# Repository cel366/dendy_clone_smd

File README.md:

# Деndи
Конструкция 8-ми битной приставки ,клона famicom. Максимально элементы применены для поверхностного монтажа . Печатная плата разработана для изготовления в домашних условиях ,поэтому для соединения дорожек на разных слоях использованы переходные отверстия ,для соединениями перемычками .  в папке FAB/lut два файла svg  с слоями верхним(уже от зеркаленным) и нижним  

Плата размером 90х90 ,чтобы можно было потом распечатать на принтере EasyThreeD K9 , у которого печатающая поверхность  100х100,корпус.

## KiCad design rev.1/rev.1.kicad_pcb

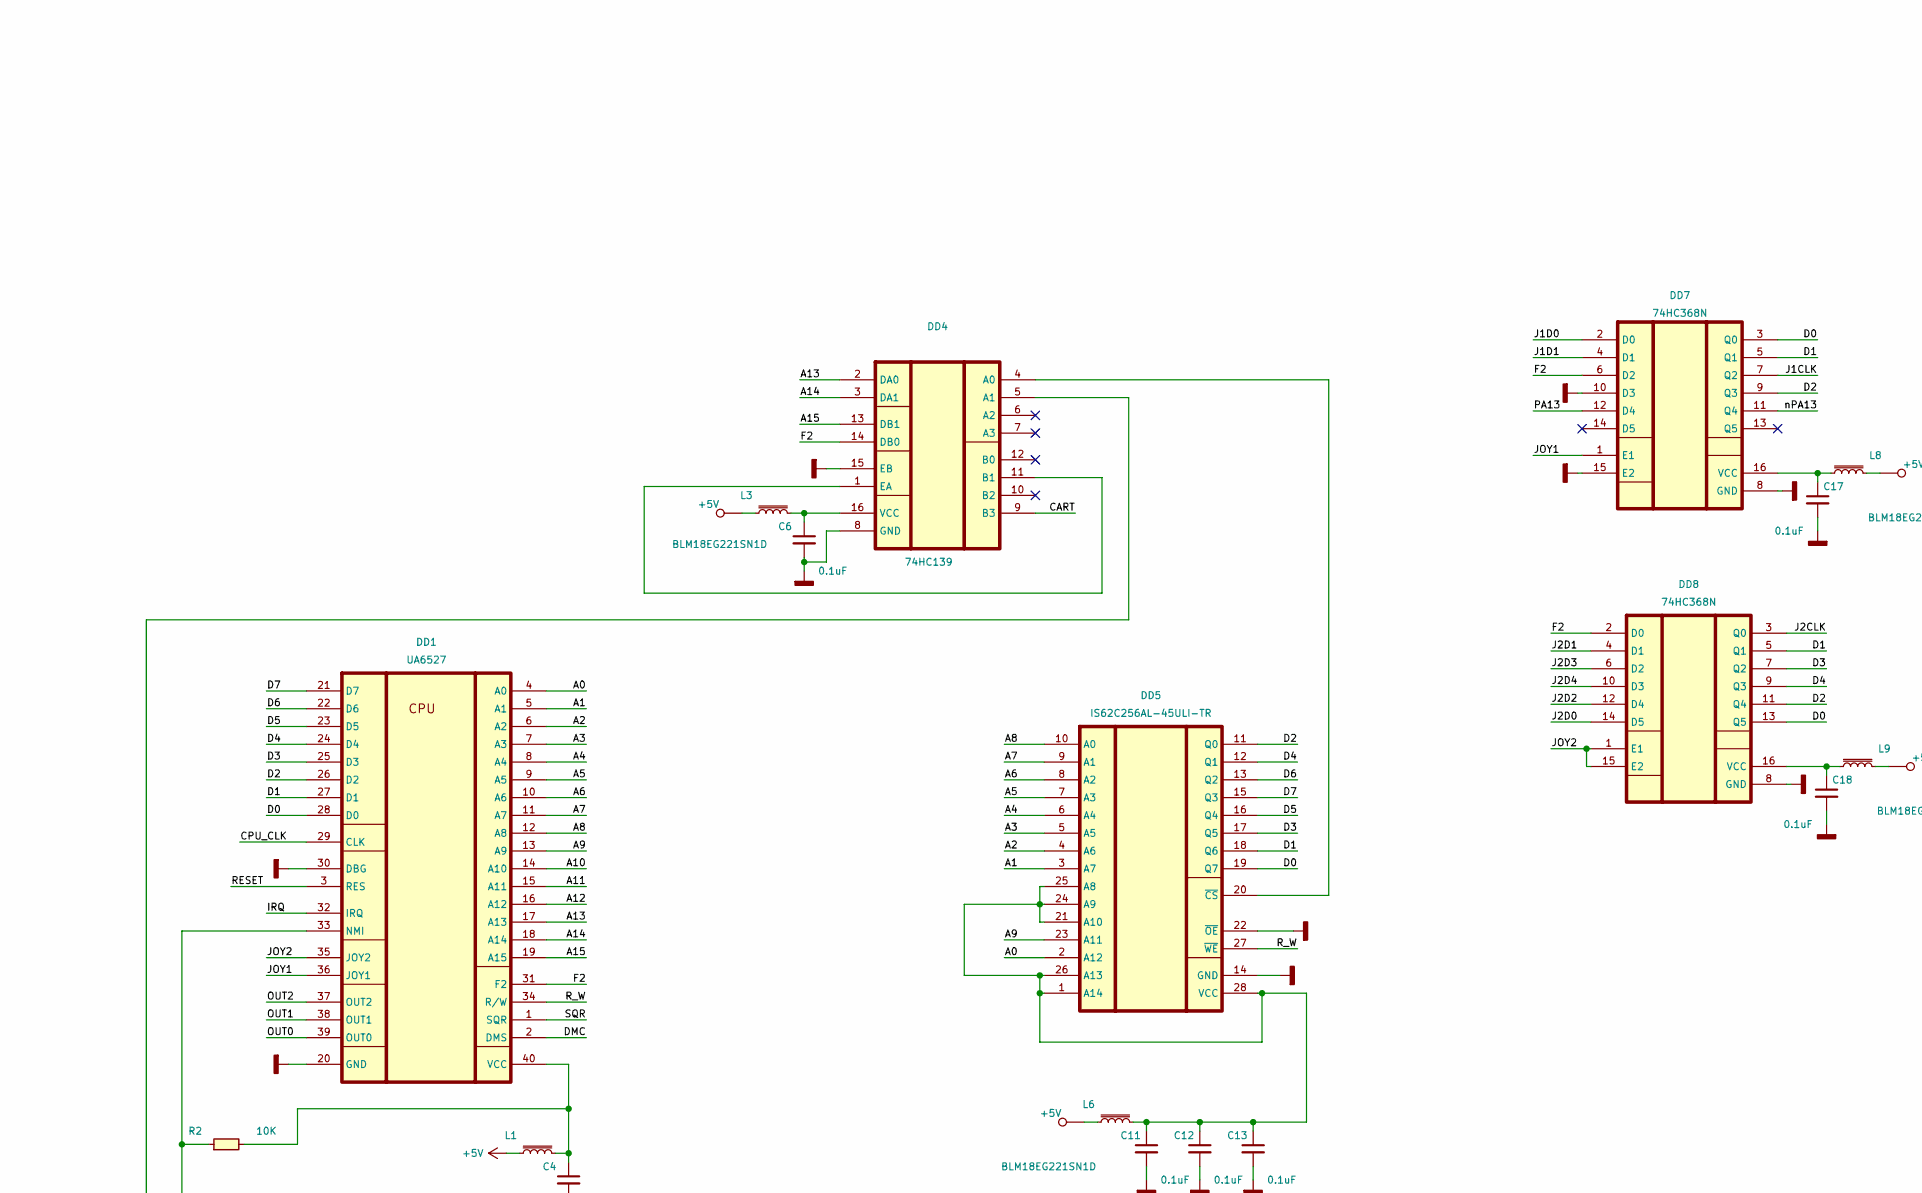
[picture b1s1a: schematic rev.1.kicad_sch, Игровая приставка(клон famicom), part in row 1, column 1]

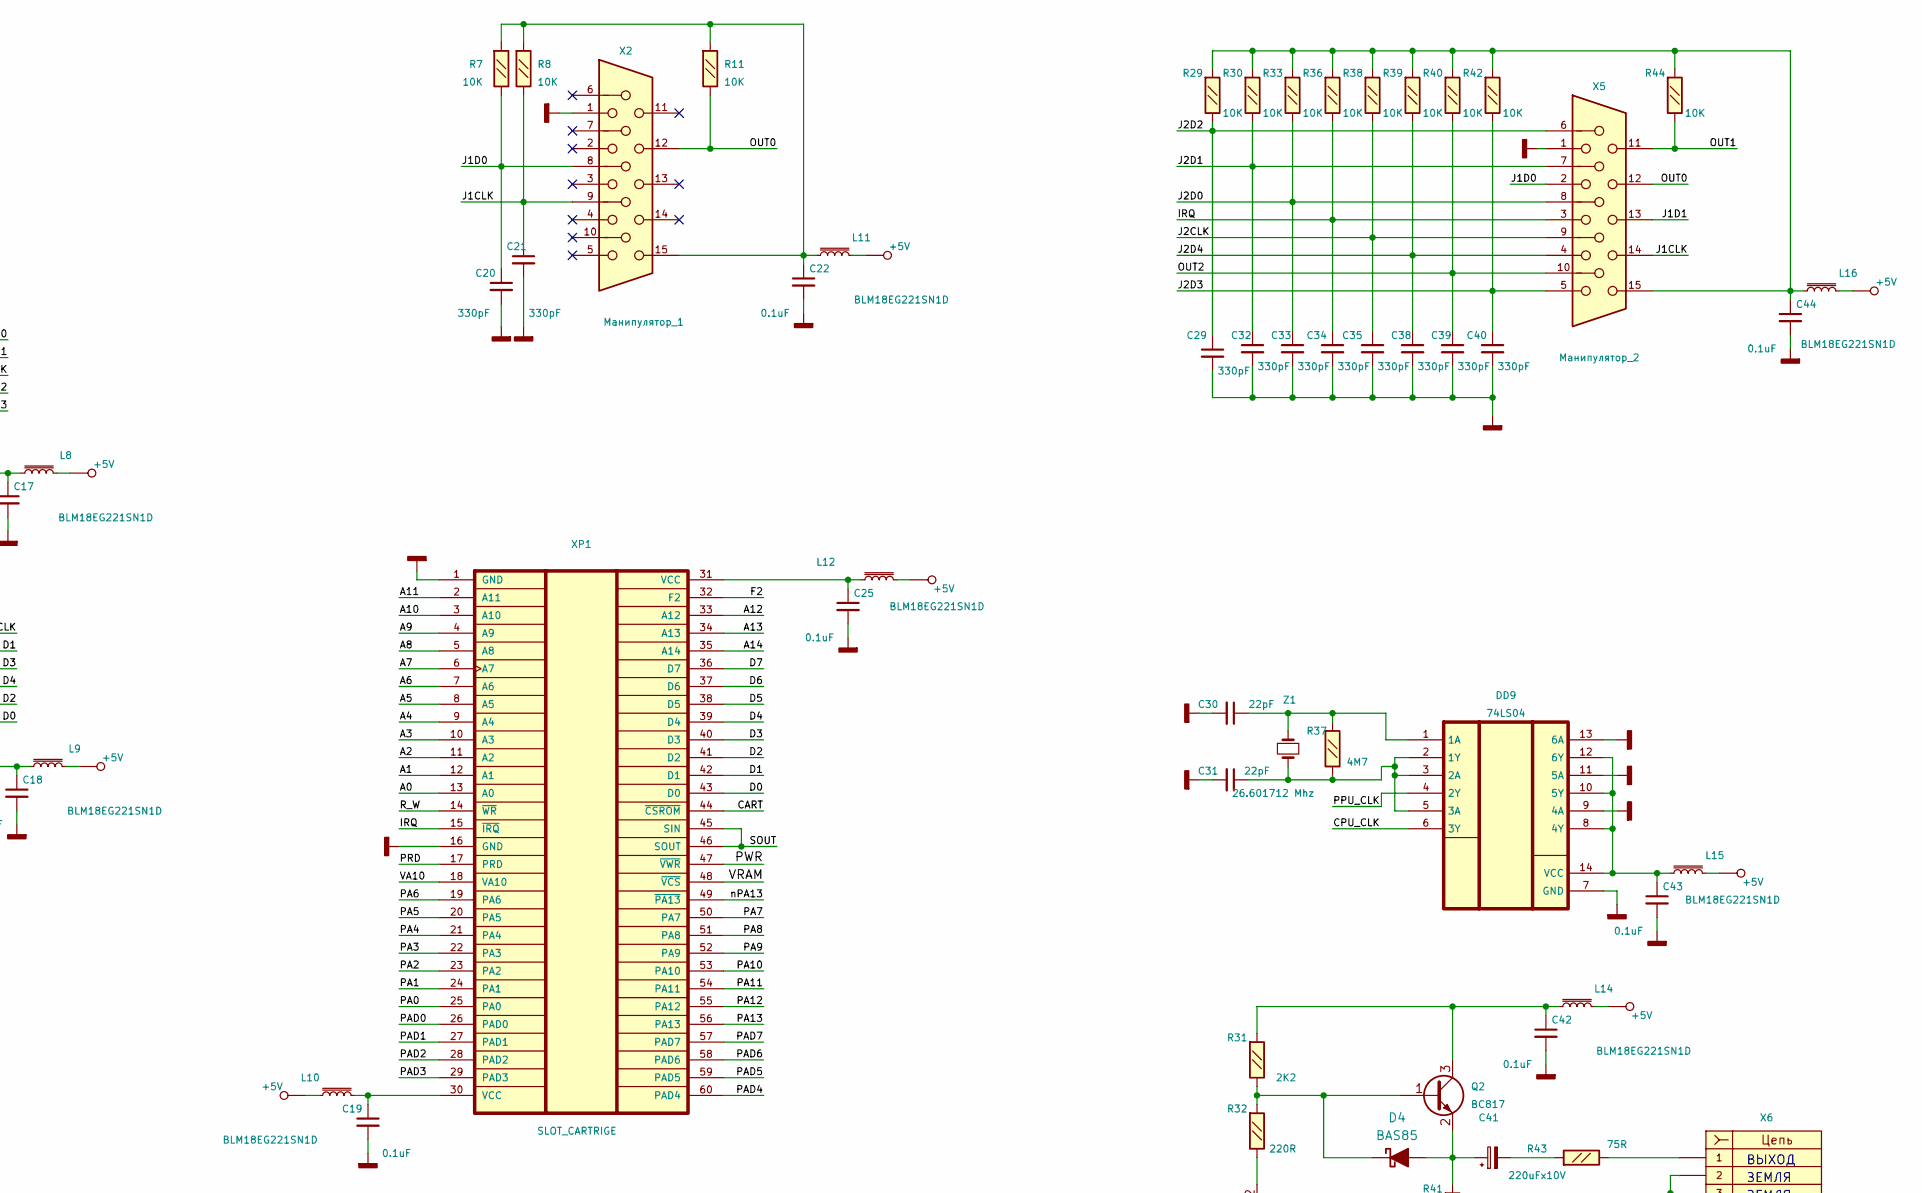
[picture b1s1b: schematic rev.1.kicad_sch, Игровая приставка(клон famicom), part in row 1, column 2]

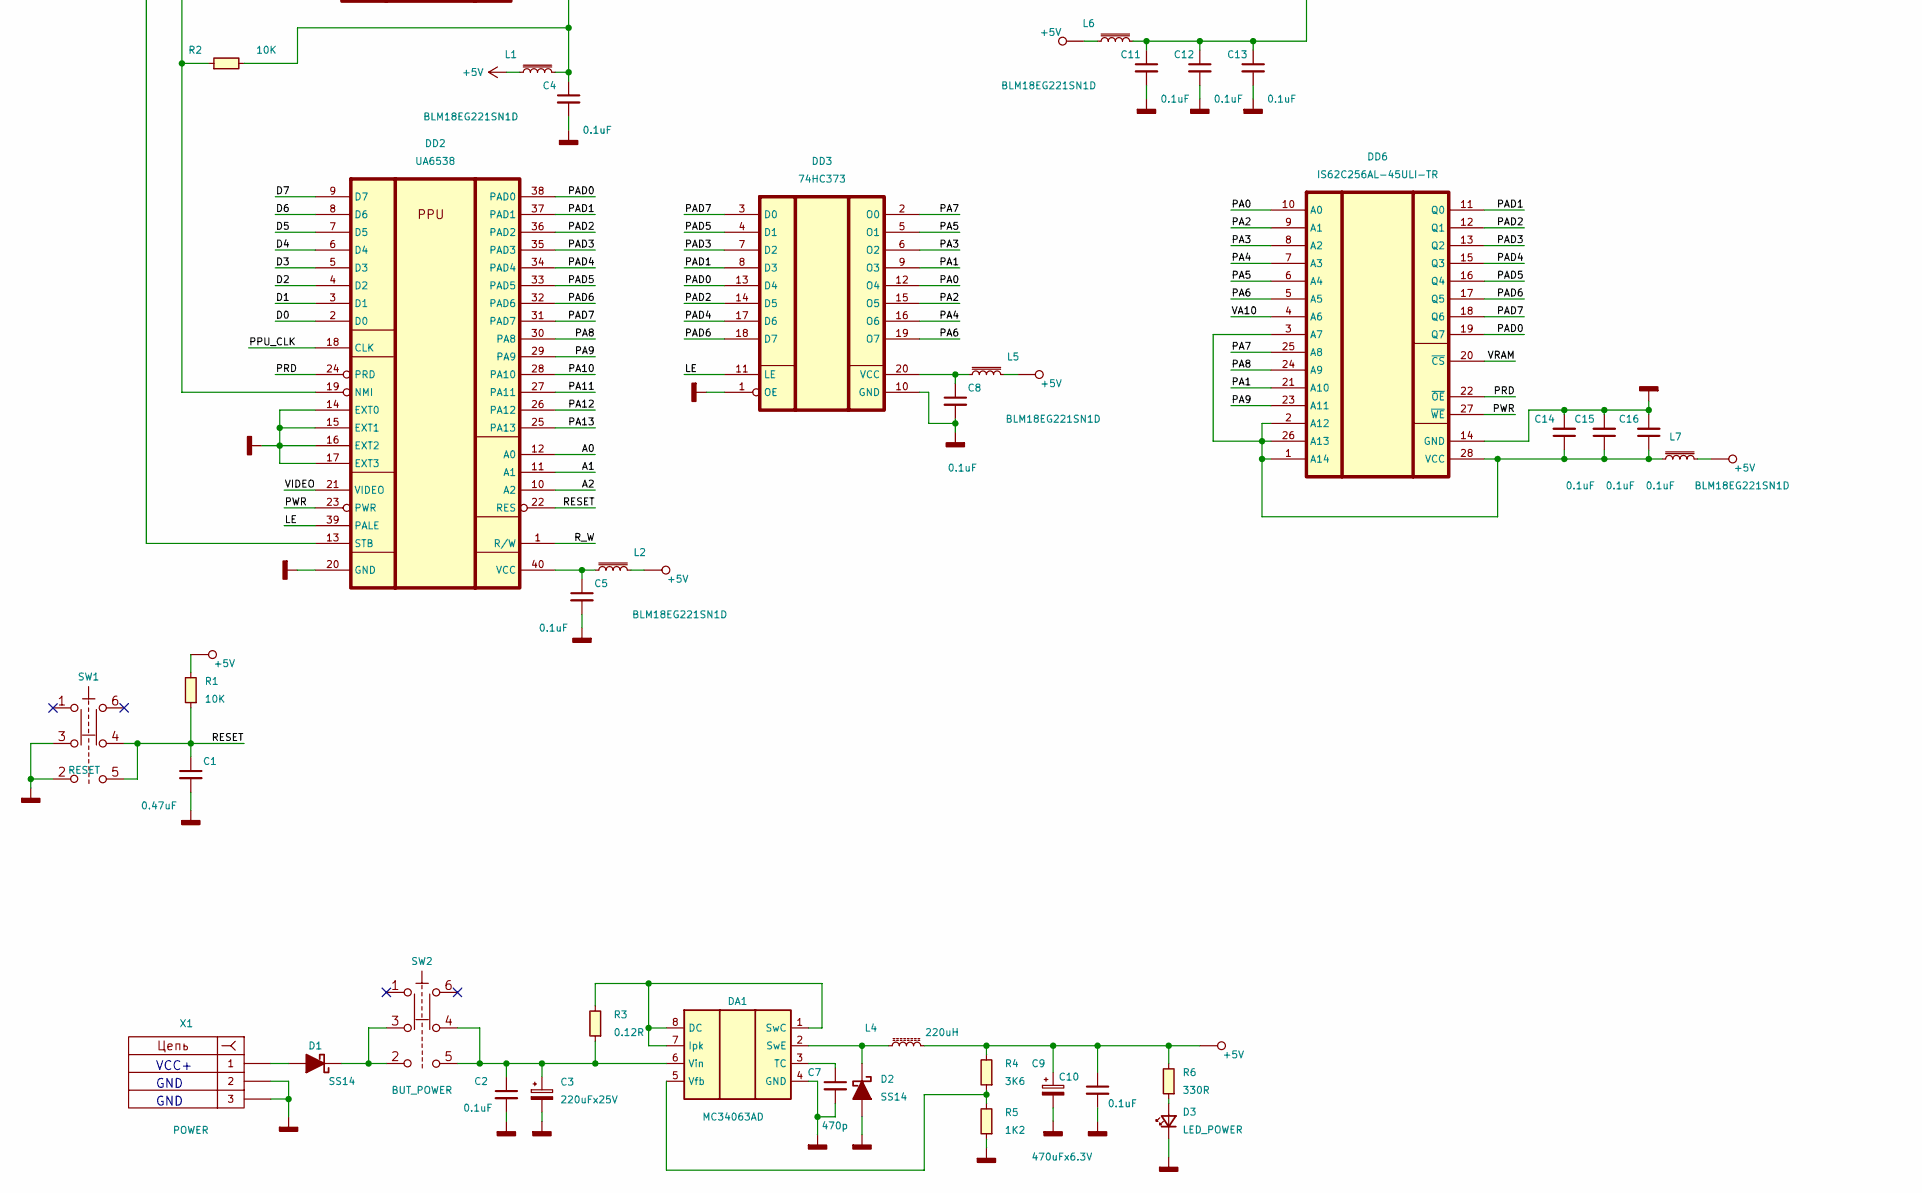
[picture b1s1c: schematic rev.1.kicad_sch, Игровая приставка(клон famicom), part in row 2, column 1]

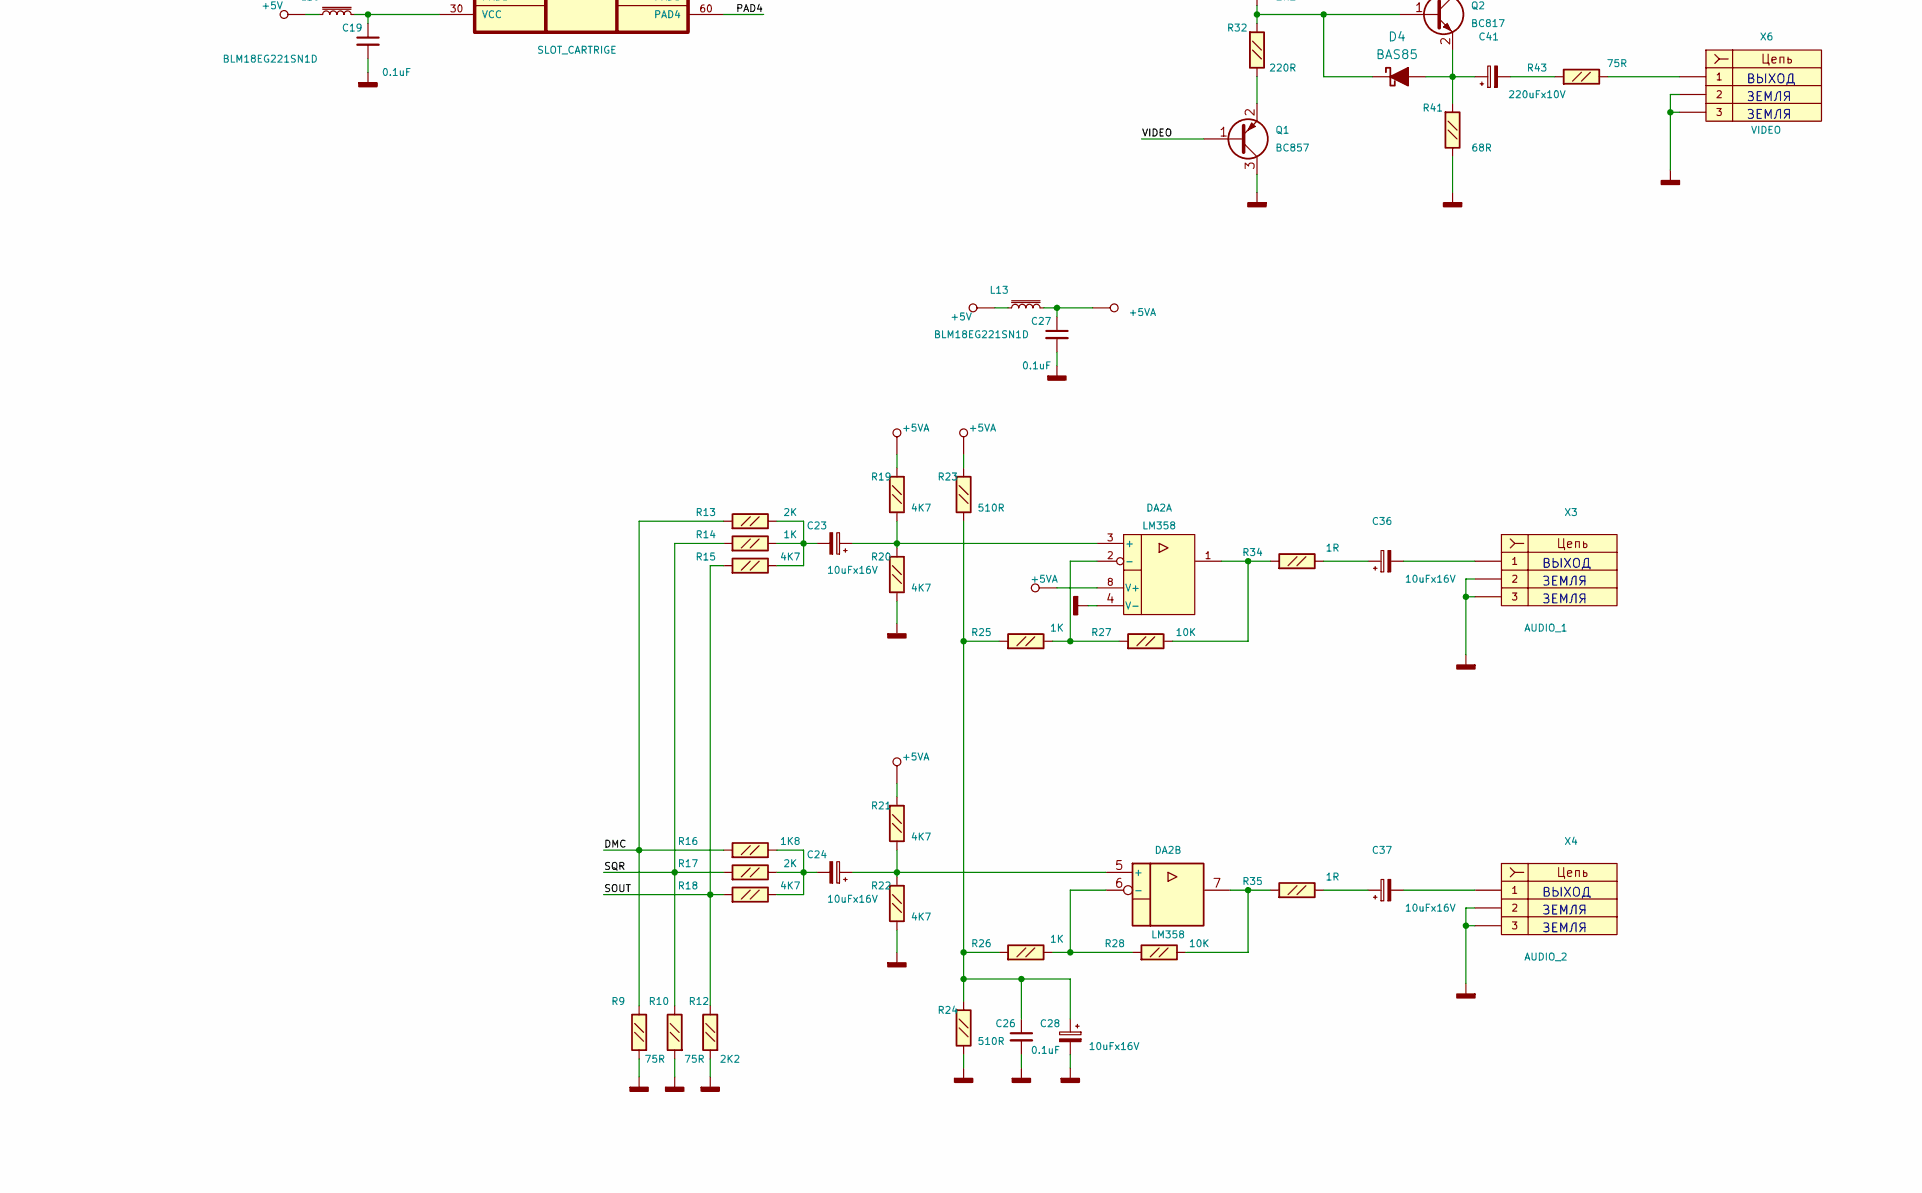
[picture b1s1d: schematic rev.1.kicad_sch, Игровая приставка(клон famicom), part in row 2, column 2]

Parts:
C1: 0.47uF; C_0603_1608Metric
C2, C4, C5, C6, C8, C10, C11, C12, C13, C14, C15, C16, C17, C18, C19, C22, C25, C26, C27, C42, C43, C44: 0.1uF; C_0603_1608Metric
C3: 220uFx25V; CP_Elec_8x10.5
C7: 470p; C_0603_1608Metric
C9: 470uFx6.3V; CP_Elec_8x10.5
C20, C21, C29, C32, C33, C34, C35, C38, C39, C40: 330pF; C_0603_1608Metric
C23, C24, C28, C36, C37: 10uFx16V; CP_Elec_4x5.4
C30, C31: 22pF; C_0603_1608Metric
C41: 220uFx10V; CP_Elec_8x6.5
D1, D2: SS14; D_SMA
D3: LED_POWER; LED_D3.0mm
D4: BAS85; D_MiniMELF
DA1: MC34063AD; SOIC-8_3.9x4.9mm_P1.27mm
DA2: LM358; SOIC-8_3.9x4.9mm_P1.27mm
DD1: UA6527; DIP-40_W15.24mm_Socket
DD2: UA6538; DIP-40_W15.24mm_Socket
DD3: 74HC373; SO-20_12.8x7.5mm_P1.27mm
DD4: 74HC139; SO-16_3.9x9.9mm_P1.27mm
DD5, DD6: IS62C256AL-45ULI-TR; SOIC-28W_7.5x17.9mm_P1.27mm
DD7, DD8: 74HC368N; SO-16_3.9x9.9mm_P1.27mm
DD9: 74LS04; SO-14_3.9x8.65mm_P1.27mm
L1, L2, L3, L5, L6, L7, L8, L9, L10, L11, L12, L13, L14, L15, L16: BLM18EG221SN1D; L_0603_1608Metric
L4: 220uH; L_Radial_D7.0mm_P3.00mm
Q1: BC857; SOT-23
Q2: BC817; SOT-23
R1, R2, R7, R8, R11, R27, R28, R29, R30, R33, R36, R38, R39, R40, R42, R44: 10K; R_0603_1608Metric
R3: 0.12R; R_0603_1608Metric
R4: 3K6; R_0603_1608Metric
R5: 1K2; R_0603_1608Metric
R6: 330R; R_0603_1608Metric
R9, R10, R43: 75R; R_0603_1608Metric
R12, R31: 2K2; R_0603_1608Metric
R13, R17: 2K; R_0603_1608Metric
R14, R25, R26: 1K; R_0603_1608Metric
R15, R18, R19, R20, R21, R22: 4K7; R_0603_1608Metric
R16: 1K8; R_0603_1608Metric
R23, R24: 510R; R_0603_1608Metric
R32: 220R; R_0603_1608Metric
R34, R35: 1R; R_0603_1608Metric
R37: 4M7; R_0603_1608Metric
R41: 68R; R_0603_1608Metric
SW1: RESET; KLS7_P8X8
SW2: BUT_POWER; KLS7_P8X8
X1: POWER; BarrelJack_Wuerth_6941xx301002
X2: Манипулятор_1; DSUB-15_Male_Horizontal_P2.77x2.84mm_EdgePinOffset4.94mm_Ho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
X3: AUDIO_1; RCA-105
X4: AUDIO_2; RCA-105
X5: Манипулятор_2; DSUB-15_Male_Horizontal_P2.77x2.84mm_EdgePinOffset4.94mm_Ho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
X6: VIDEO; RCA-105
XP1: SLOT_CARTRIGE; 60 PIN FAMICOM CARTRIDGE SLOT
Z1: 26.601712 Mhz; Crystal_SMD_HC49-SD

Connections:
+5V: C9.1, C10.1, L1.1, L2.1, L3.1, L4.2, L5.1, L6.1, L7.1, L8.1, L9.1, L10.1, L11.1, L12.1, L13.1, L14.1, L15.1, L16.1, R1.2, R4.2, R6.2
+5VA: C27.1, DA2.8 (V+), L13.2, R19.2, R21.2, R23.2
/A0: DD1.4 (A0), DD2.12 (A0), DD5.2 (A12), XP1.13 (A0)
/A1: DD1.5 (A1), DD2.11 (A1), DD5.3 (A7), XP1.12 (A1)
/A2: DD1.6 (A2), DD2.10 (A2), DD5.4 (A6), XP1.11 (A2)
/A3: DD1.7 (A3), DD5.5 (A5), XP1.10 (A3)
/A4: DD1.8 (A4), DD5.6 (A4), XP1.9 (A4)
/A5: DD1.9 (A5), DD5.7 (A3), XP1.8 (A5)
/A6: DD1.10 (A6), DD5.8 (A2), XP1.7 (A6)
/A7: DD1.11 (A7), DD5.9 (A1), XP1.6 (A7)
/A8: DD1.12 (A8), DD5.10 (A0), XP1.5 (A8)
/A9: DD1.13 (A9), DD5.23 (A11), XP1.4 (A9)
/A10: DD1.14 (A10), XP1.3 (A10)
/A11: DD1.15 (A11), XP1.2 (A11)
/A12: DD1.16 (A12), XP1.33 (A12)
/A13: DD1.17 (A13), DD4.2 (DA0), XP1.34 (A13)
/A14: DD1.18 (A14), DD4.3 (DA1), XP1.35 (A14)
/A15: DD1.19 (A15), DD4.13 (DB1)
/CART: DD4.9 (B3), XP1.44 (~CSROM)
/CPU_CLK: DD1.29 (CLK), DD9.6 (3Y)
/D0: DD1.28 (D0), DD2.2 (D0), DD5.19 (Q7), DD7.3 (Q0), DD8.13 (Q5), XP1.43 (D0)
/D1: DD1.27 (D1), DD2.3 (D1), DD5.18 (Q6), DD7.5 (Q1), DD8.5 (Q1), XP1.42 (D1)
/D2: DD1.26 (D2), DD2.4 (D2), DD5.11 (Q0), DD7.9 (Q3), DD8.11 (Q4), XP1.41 (D2)
/D3: DD1.25 (D3), DD2.5 (D3), DD5.17 (Q5), DD8.7 (Q2), XP1.40 (D3)
/D4: DD1.24 (D4), DD2.6 (D4), DD5.12 (Q1), DD8.9 (Q3), XP1.39 (D4)
/D5: DD1.23 (D5), DD2.7 (D5), DD5.16 (Q4), XP1.38 (D5)
/D6: DD1.22 (D6), DD2.8 (D6), DD5.13 (Q2), XP1.37 (D6)
/D7: DD1.21 (D7), DD2.9 (D7), DD5.15 (Q3), XP1.36 (D7)
/DMC: DD1.2 (DMS), R9.1, R13.2, R16.2
/F2: DD1.31 (F2), DD4.14 (DB0), DD7.6 (D2), DD8.2 (D0), XP1.32 (F2)
/IRQ: C34.1, DD1.32 (IRQ), R36.1, X5.3, XP1.15 (~IRQ)
/J1CLK: C21.1, DD7.7 (Q2), R8.1, X2.9, X5.14
/J1D0: C20.1, DD7.2 (D0), R7.1, X2.8, X5.2
/J1D1: DD7.4 (D1), X5.13
/J2CLK: C35.1, DD8.3 (Q0), R38.1, X5.9
/J2D0: C33.1, DD8.14 (D5), R33.1, X5.8
/J2D1: C32.1, DD8.4 (D1), R30.1, X5.7
/J2D2: C29.1, DD8.12 (D4), R29.1, X5.6
/J2D3: C40.1, DD8.6 (D2), R42.1, X5.5
/J2D4: C38.1, DD8.10 (D3), R39.1, X5.4
/JOY1: DD1.36 (JOY1), DD7.1 (E1)
/JOY2: DD1.35 (JOY2), DD8.1 (E1), DD8.15 (E2)
/LE: DD2.39 (PALE), DD3.11 (LE)
/OUT0: DD1.39 (OUT0), R11.1, X2.12, X5.12
/OUT1: DD1.38 (OUT1), R44.1, X5.11
/OUT2: C39.1, DD1.37 (OUT2), R40.1, X5.10
/PA0: DD3.12 (O4), DD6.10 (A0), XP1.25 (PA0)
/PA1: DD3.9 (O3), DD6.21 (A10), XP1.24 (PA1)
/PA2: DD3.15 (O5), DD6.9 (A1), XP1.23 (PA2)
/PA3: DD3.6 (O2), DD6.8 (A2), XP1.22 (PA3)
/PA4: DD3.16 (O6), DD6.7 (A3), XP1.21 (PA4)
/PA5: DD3.5 (O1), DD6.6 (A4), XP1.20 (PA5)
/PA6: DD3.19 (O7), DD6.5 (A5), XP1.19 (PA6)
/PA7: DD3.2 (O0), DD6.25 (A8), XP1.50 (PA7)
/PA8: DD2.30 (PA8), DD6.24 (A9), XP1.51 (PA8)
/PA9: DD2.29 (PA9), DD6.23 (A11), XP1.52 (PA9)
/PA10: DD2.28 (PA10), XP1.53 (PA10)
/PA11: DD2.27 (PA11), XP1.54 (PA11)
/PA12: DD2.26 (PA12), XP1.55 (PA12)
/PA13: DD2.25 (PA13), DD7.12 (D4), XP1.56 (PA13)
/PAD0: DD2.38 (PAD0), DD3.13 (D4), DD6.19 (Q7), XP1.26 (PAD0)
/PAD1: DD2.37 (PAD1), DD3.8 (D3), DD6.11 (Q0), XP1.27 (PAD1)
/PAD2: DD2.36 (PAD2), DD3.14 (D5), DD6.12 (Q1), XP1.28 (PAD2)
/PAD3: DD2.35 (PAD3), DD3.7 (D2), DD6.13 (Q2), XP1.29 (PAD3)
/PAD4: DD2.34 (PAD4), DD3.17 (D6), DD6.15 (Q3), XP1.60 (PAD4)
/PAD5: DD2.33 (PAD5), DD3.4 (D1), DD6.16 (Q4), XP1.59 (PAD5)
/PAD6: DD2.32 (PAD6), DD3.18 (D7), DD6.17 (Q5), XP1.58 (PAD6)
/PAD7: DD2.31 (PAD7), DD3.3 (D0), DD6.18 (Q6), XP1.57 (PAD7)
/PPU_CLK: DD2.18 (CLK), DD9.4 (2Y)
/PRD: DD2.24 (PRD), DD6.22 (~OE), XP1.17 (PRD)
/PWR: DD2.23 (PWR), DD6.27 (~WE), XP1.47 (~VWR)
/RESET: C1.1, DD1.3 (RES), DD2.22 (RES), R1.1, SW1.4, SW1.5
/R_W: DD1.34 (R/W), DD2.1 (R/W), DD5.27 (~WE), XP1.14 (~WR)
/SOUT: R12.1, R15.2, R18.2, XP1.45 (SIN), XP1.46 (SOUT)
/SQR: DD1.1 (SQR), R10.1, R14.2, R17.2
/VA10: DD6.4 (A6), XP1.18 (VA10)
/VIDEO: DD2.21 (VIDEO), Q1.1 (B)
/VRAM: DD6.20 (~CS), XP1.48 (~VCS)
/nPA13: DD7.11 (Q4), XP1.49 (~PA13)
GNDD: C1.2, C2.2, C3.2, C4.2, C5.2, C6.2, C7.2, C8.2, C9.2, C10.2, C11.2, C12.2, C13.2, C14.2, C15.2, C16.2, C17.2, C18.2, C19.2, C20.2, C21.2, C22.2, C25.2, C26.2, C27.2, C28.2, C29.2, C30.2, C31.2, C32.2, C33.2, C34.2, C35.2, C38.2, C39.2, C40.2, C42.2, C43.2, C44.2, D2.2 (A), D3.1 (K), DA1.4 (GND), DA2.4 (V-), DD1.20 (GND), DD1.30 (DBG), DD2.14 (EXT0), DD2.15 (EXT1), DD2.16 (EXT2), DD2.17 (EXT3), DD2.20 (GND), DD3.1 (OE), DD3.10 (GND), DD4.8 (GND), DD4.15 (EB), DD5.14 (GND), DD5.22 (~OE), DD6.14 (GND), DD7.8 (GND), DD7.10 (D3), DD7.15 (E2), DD8.8 (GND), DD9.7 (GND), DD9.9 (4A), DD9.11 (5A), DD9.13 (6A), Q1.3 (C), R5.1, R9.2, R10.2, R12.2, R20.1, R22.1, R24.1, R41.1, SW1.2, SW1.3, X1.2, X1.3, X2.1, X3.2, X3.3, X4.2, X4.3, X5.1, X6.2, X6.3, XP1.1 (GND), XP1.16 (GND)
unnamed: C19.1, L10.2, XP1.30 (VCC)
unnamed: C22.1, L11.2, R7.2, R8.2, R11.2, X2.15
unnamed: C23.2, R13.1, R14.1, R15.1
unnamed: C24.2, R16.1, R17.1, R18.1
unnamed: C25.1, L12.2, XP1.31 (VCC)
unnamed: C26.1, C28.1, R23.1, R24.2, R25.2, R26.2
unnamed: C36.1, R34.1
unnamed: C37.1, R35.1
unnamed: C41.2, R43.2
unnamed: C44.1, L16.2, R29.2, R30.2, R33.2, R36.2, R38.2, R39.2, R40.2, R42.2, R44.2, X5.15
unnamed: D1.2 (A), X1.1
unnamed: D1.1 (K), SW2.2, SW2.3
unnamed: D2.1 (K), DA1.2 (SwE), L4.1
unnamed: D3.2 (A), R6.1
unnamed: C41.1, D4.2 (A), Q2.2 (E), R41.2
unnamed: D4.1 (K), Q2.1 (B), R31.1, R32.2
unnamed: DA1.1 (SwC), DA1.7 (Ipk), DA1.8 (DC), R3.2
unnamed: C7.1, DA1.3 (TC)
unnamed: DA1.5 (Vfb), R4.1, R5.2
unnamed: C2.1, C3.1, DA1.6 (Vin), R3.1, SW2.4, SW2.5
unnamed: DA2.1, R27.1, R34.2
unnamed: DA2.7, R28.1, R35.2
unnamed: C23.1, DA2.3 (+), R19.1, R20.2
unnamed: DA2.2 (-), R25.1, R27.2
unnamed: C24.1, DA2.5 (+), R21.1, R22.2
unnamed: DA2.6 (-), R26.1, R28.2
unnamed: DD1.33 (NMI), DD2.19 (NMI), R2.1
unnamed: C4.1, DD1.40 (VCC), L1.2, R2.2
unnamed: DD2.13 (STB), DD4.5 (A1)
unnamed: C5.1, DD2.40 (VCC), L2.2
unnamed: C8.1, DD3.20 (VCC), L5.2
unnamed: DD4.4 (A0), DD5.20 (~CS)
unnamed: DD4.1 (EA), DD4.11 (B1)
unnamed: C6.1, DD4.16 (VCC), L3.2
unnamed: C11.1, C12.1, C13.1, DD5.1 (A14), DD5.21 (A10), DD5.24 (A9), DD5.25 (A8), DD5.26 (A13), DD5.28 (VCC), L6.2
unnamed: C14.1, C15.1, C16.1, DD6.1 (A14), DD6.2 (A12), DD6.3 (A7), DD6.26 (A13), DD6.28 (VCC), L7.2
unnamed: C17.1, DD7.16 (VCC), L8.2
unnamed: C18.1, DD8.16 (VCC), L9.2
unnamed: C30.1, DD9.1 (1A), R37.2, Z1.1
unnamed: C31.1, DD9.2 (1Y), DD9.3 (2A), DD9.5 (3A), R37.1, Z1.2
unnamed: C43.1, DD9.8 (4Y), DD9.10 (5Y), DD9.12 (6Y), DD9.14 (VCC), L15.2
unnamed: Q1.2 (E), R32.1
unnamed: C42.1, L14.2, Q2.3 (C), R31.2
unnamed: C36.2, X3.1
unnamed: C37.2, X4.1
unnamed: R43.1, X6.1

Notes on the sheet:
ВЫХОД
ЗЕМЛЯ
GND
VCC+

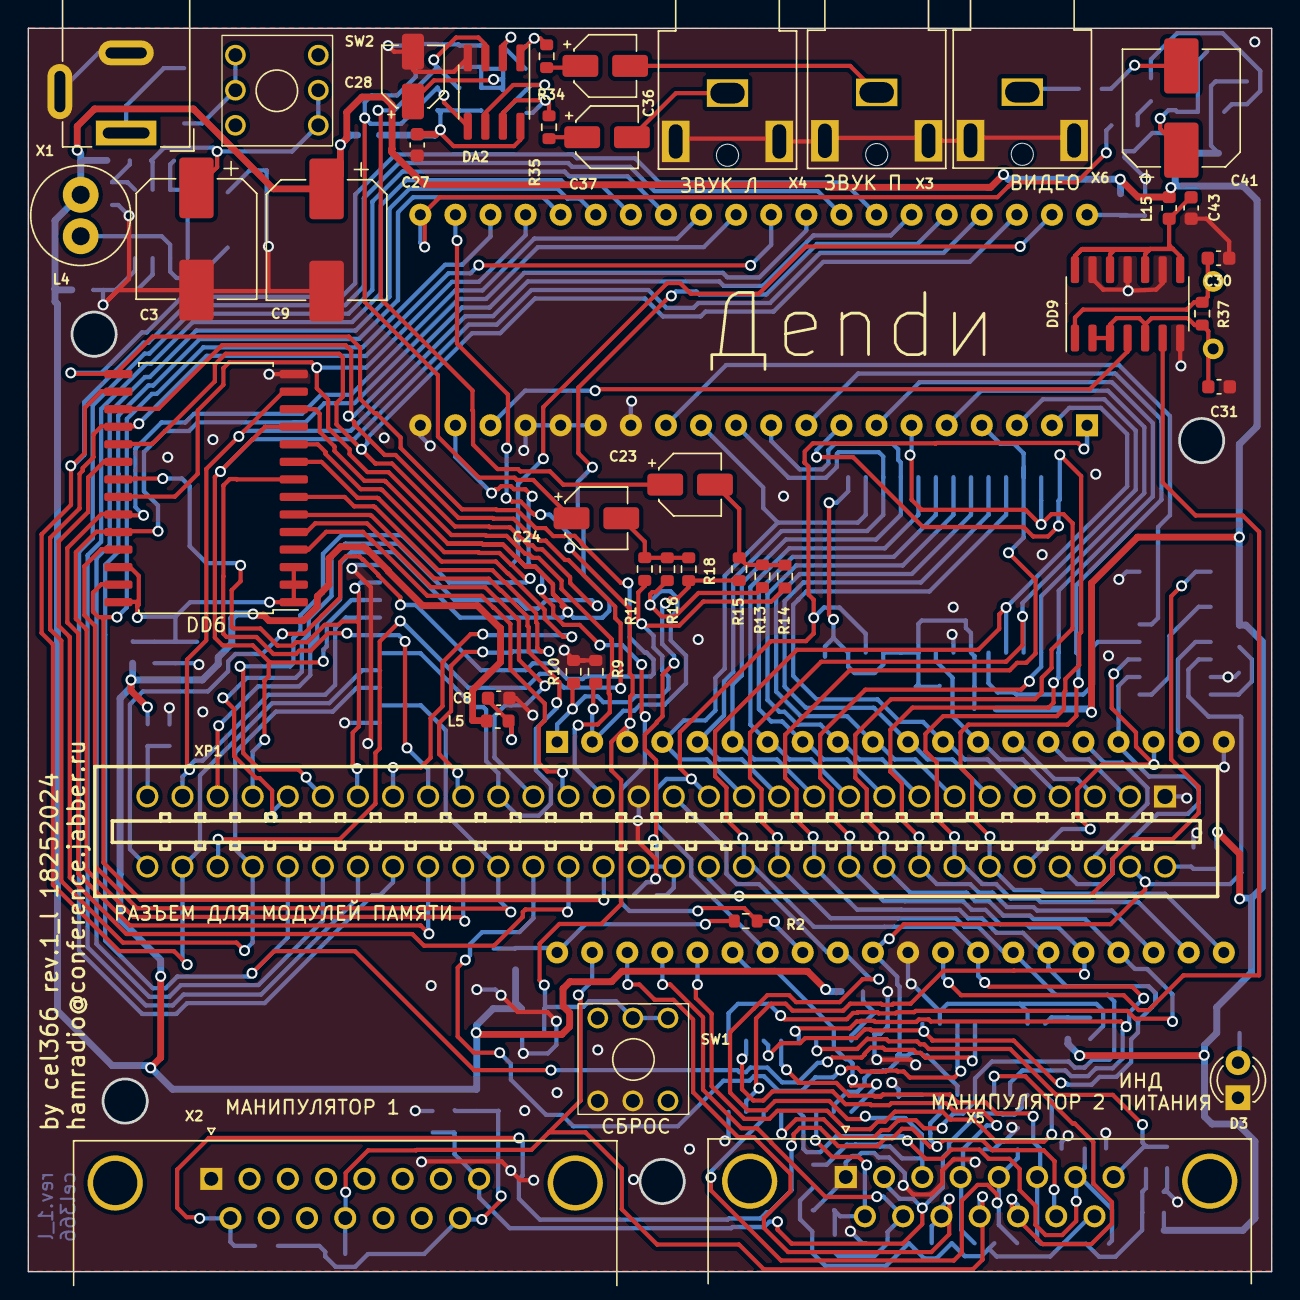
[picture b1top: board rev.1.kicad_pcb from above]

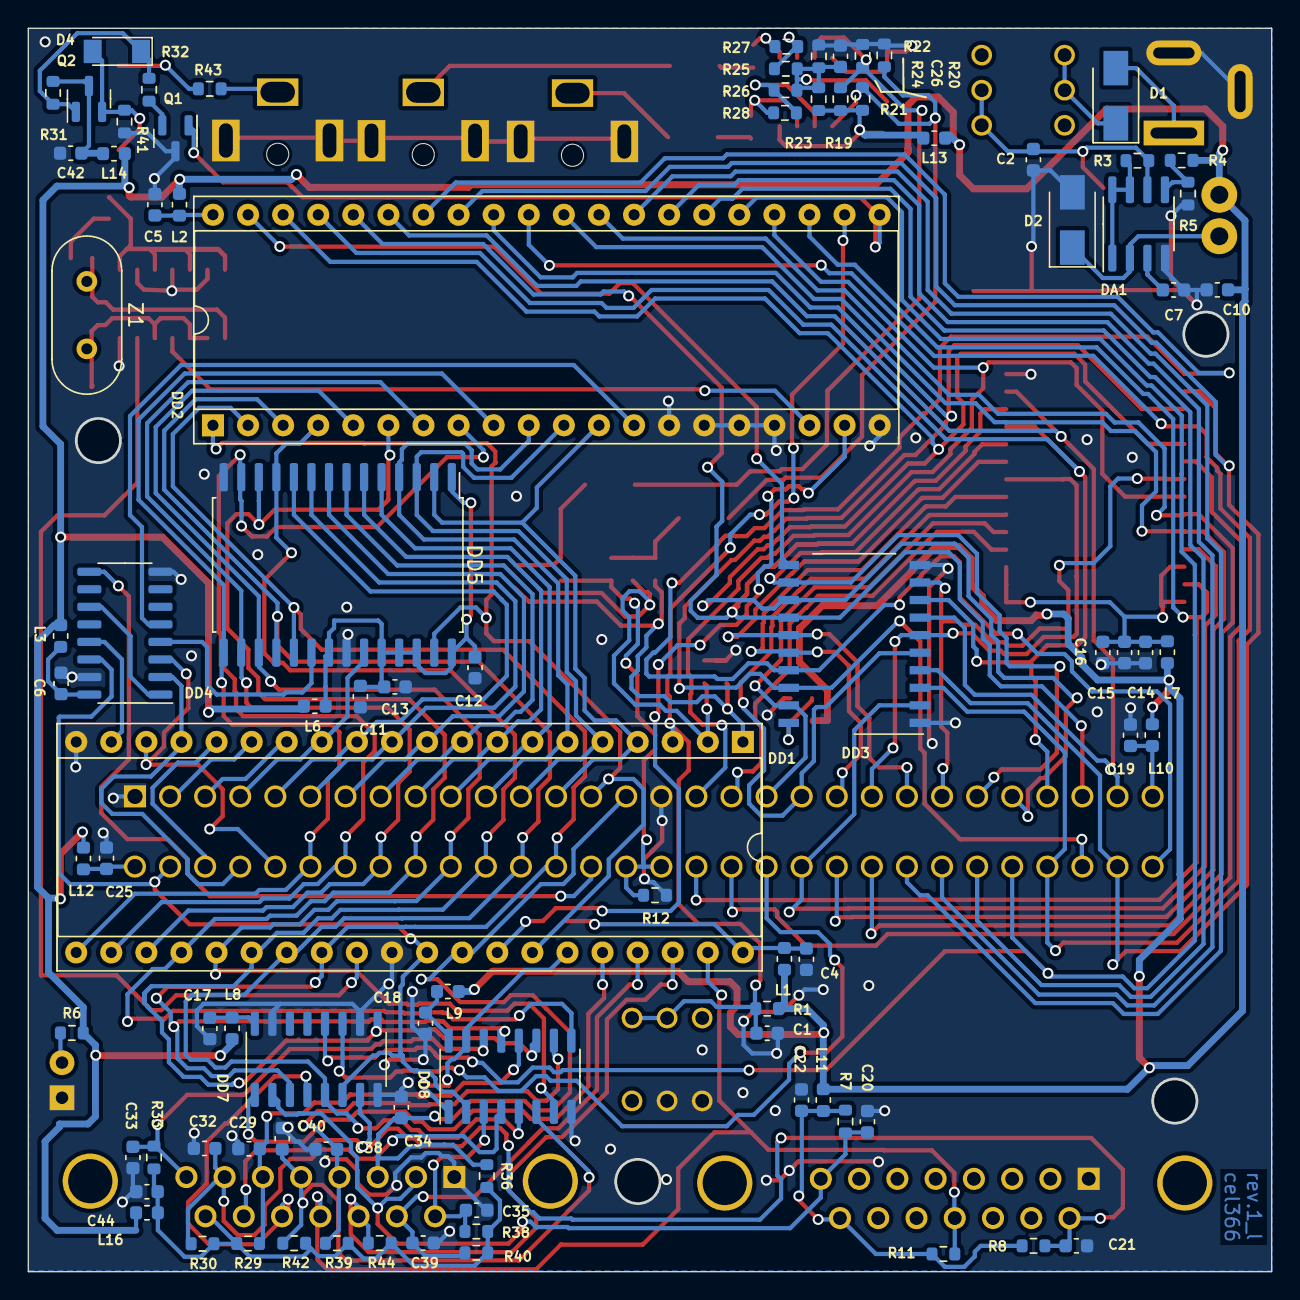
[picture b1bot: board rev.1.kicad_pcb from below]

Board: 2 copper layers, 90.0 x 90.0 mm, 131 parts (90 on the bottom side), 126 nets.

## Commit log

2022-12-22 Сделал цифровую часть и один джойстик
2022-12-22 убрал иерархию
2022-12-27 добавил документацию опринципах работы приставки и доделал джойстики
2023-03-23 добавил видеоусилитель
2023-03-23 добавил генератор частоты на 74ls04
2023-03-23 закончил схему звукового вывода
2023-06-09 Добавил стабилизатор питания и закончил схему
2023-07-13 сделал контур платы и начал раставлять элементц
2023-08-26 раставил элементы приступил к трассеровке
2024-06-18 Сделал разводку печатной платы
2024-06-18 Добавил схему в pdf
2024-06-18 расставил обозначения и надписи
2024-06-18 мелкие улучшения и добавление крепежных отверстий
2024-06-27 добавил список элементов ,гербера
2024-06-27 Update README.md
    описание
2024-06-27 Update README.md
    readme
2025-01-27 Исправил посадочные места DD5 и DD6 заново сделал файлы svg для ЛУТ , изменил название ревизии rev.1_l
2025-01-27 Сделал разводку для заводского исполения назвал ревия rev.1_F
